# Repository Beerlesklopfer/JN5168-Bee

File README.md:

# JN5168-Bee
Interface and programming Board for JN5168-001-M00Z Module and clones

Annotiantion:</br>
To prevent that some asian manufactuers take profit without any efforts, the schematic and the board mismatch.

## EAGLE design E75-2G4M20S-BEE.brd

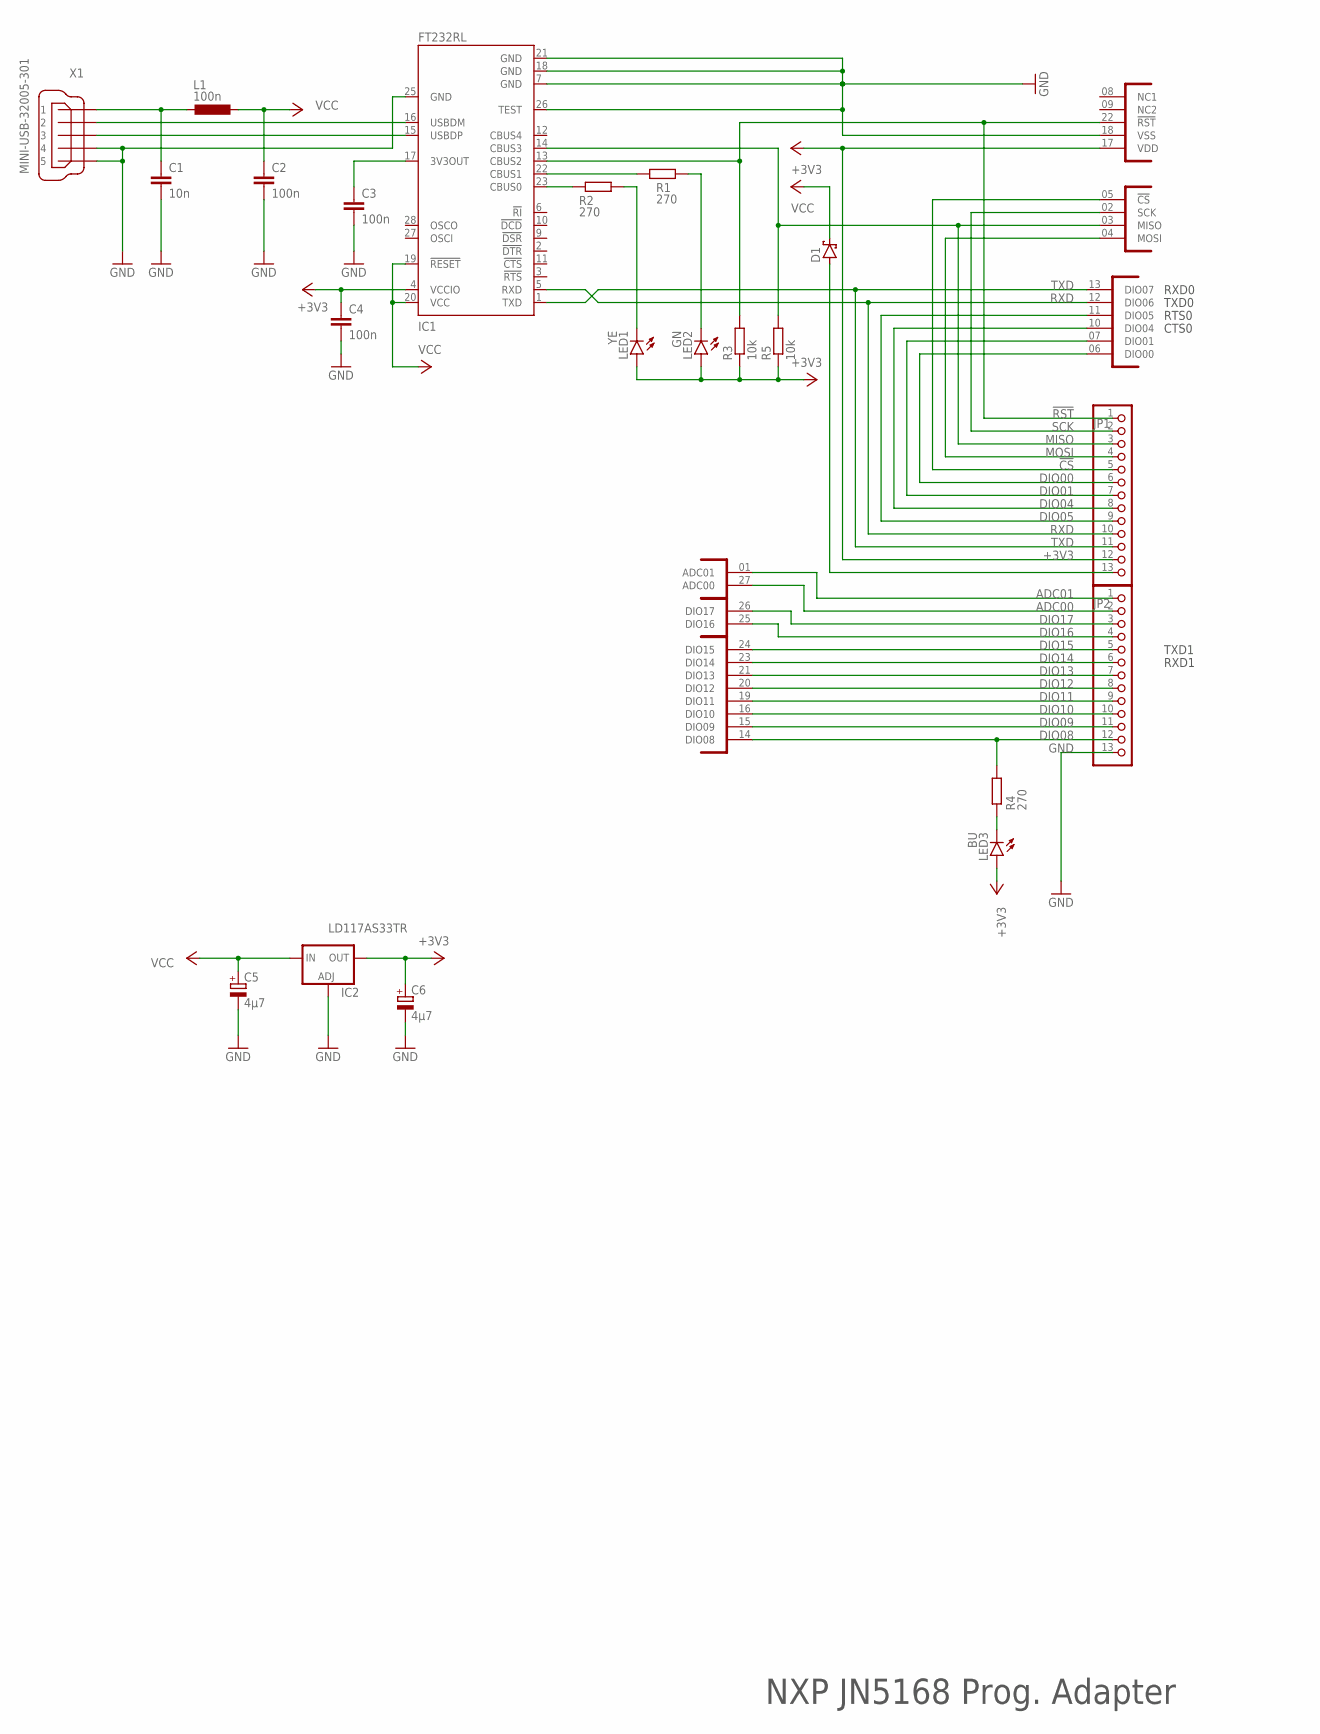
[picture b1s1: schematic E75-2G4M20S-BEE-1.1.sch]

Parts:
C1: 10n; C0805
C2, C3, C4: 100n; C0805
C5, C6: 4µ7; SMC_B
D1: SCHOTTKY-DIODESMD; SMB
IC1: FT232RL; SSOP28
IC2: LD117AS33TR; SOT223
JP1, JP2: PINHD-1X13; 1X13
L1: 100n; L3225P
LED1: YE; CHIP-LED0805
LED2: GN; CHIP-LED0805
LED3: BU; CHIP-LED0805
N1: E75-2G4M20S
R1, R2, R4: 270; R0805W
R3, R5: 10k; M0805
X1: MINI-USB-32005-301; 32005-301

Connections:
!CS: JP1.5, N1.05 (!CS)
!RST: IC1.13 (CBUS2), JP1.1, N1.22 (!RST), R3.2
+3V3: C4.1, C6.+, IC1.4 (VCCIO), IC2.4 (OUT), JP1.12, LED1.A, LED2.A, LED3.A, N1.17 (VDD), R3.1, R5.1
ADC00: JP2.2, N1.27 (ADC00)
ADC01: JP2.1, N1.01 (ADC01)
DIO00: JP1.6, N1.06 (DIO00)
DIO01: JP1.7, N1.07 (DIO01)
DIO04: JP1.8, N1.10 (DIO04)
DIO05: JP1.9, N1.11 (DIO05)
DIO06: IC1.5 (RXD), JP1.10, N1.12 (DIO06)
DIO07: IC1.1 (TXD), JP1.11, N1.13 (DIO07)
DIO08: JP2.12, N1.14 (DIO08), R4.2
DIO09: JP2.11, N1.15 (DIO09)
DIO10: JP2.10, N1.16 (DIO10)
DIO11: JP2.9, N1.19 (DIO11)
DIO12: JP2.8, N1.20 (DIO12)
DIO13: JP2.7, N1.21 (DIO13)
DIO14: JP2.6, N1.23 (DIO14)
DIO15: JP2.5, N1.24 (DIO15)
DIO16: JP2.4, N1.25 (DIO16)
DIO17: JP2.3, N1.26 (DIO17)
DM: IC1.16 (USBDM), X1.2
DP: IC1.15 (USBDP), X1.3
GND: C1.2, C2.2, C3.2, C4.2, C5.-, C6.-, IC1.7 (GND), IC1.18 (GND), IC1.21 (GND), IC1.25 (GND), IC1.26 (TEST), IC2.1 (ADJ), JP2.13, N1.18 (VSS), X1.4, X1.5
MISO: IC1.14 (CBUS3), JP1.3, N1.03 (MISO), R5.2
MOSI: JP1.4, N1.04 (MOSI)
unnamed: C3.1, IC1.17 (3V3OUT)
unnamed: LED3.C, R4.1
unnamed: C1.1, L1.2, X1.1
unnamed: IC1.23 (CBUS0), R2.1
unnamed: D1.A, JP1.13
unnamed: IC1.22 (CBUS1), R1.1
unnamed: LED1.C, R2.2
unnamed: LED2.C, R1.2
SCK: JP1.2, N1.02 (SCK)
VCC: C2.1, C5.+, D1.C, IC1.19 (!RESET), IC1.20 (VCC), IC2.3 (IN), L1.1

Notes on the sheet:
NXP JN5168 Prog. Adapter
TXD0
RXD0
RTS0
CTS0
TXD1
RXD1

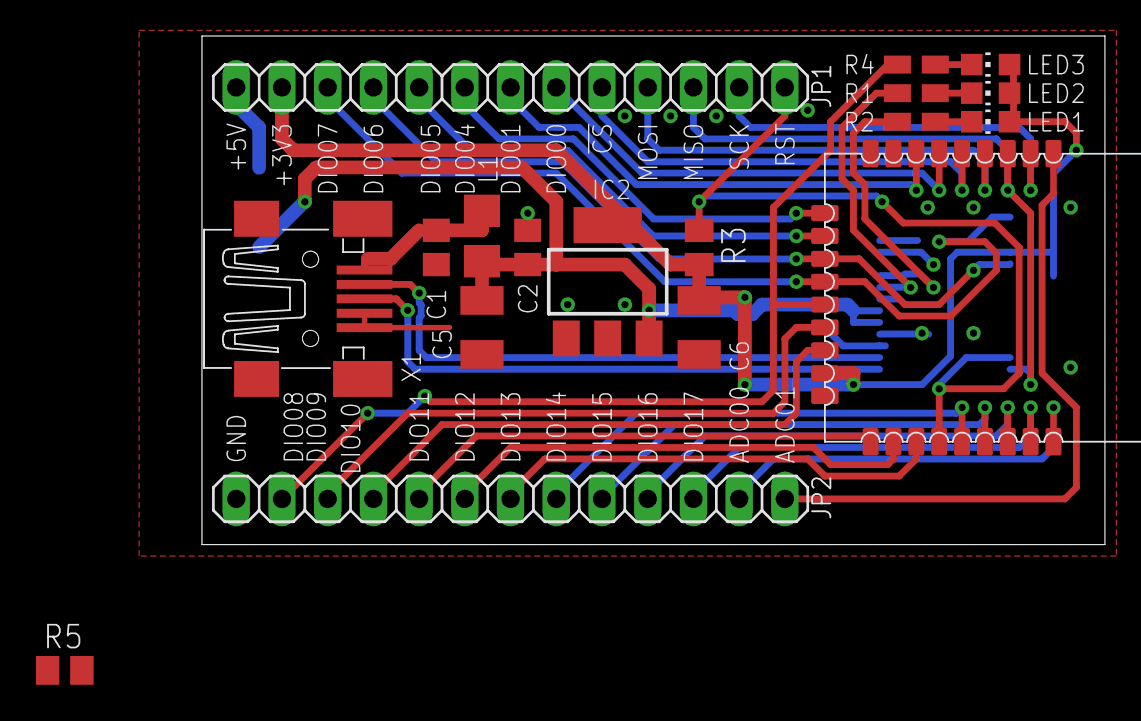
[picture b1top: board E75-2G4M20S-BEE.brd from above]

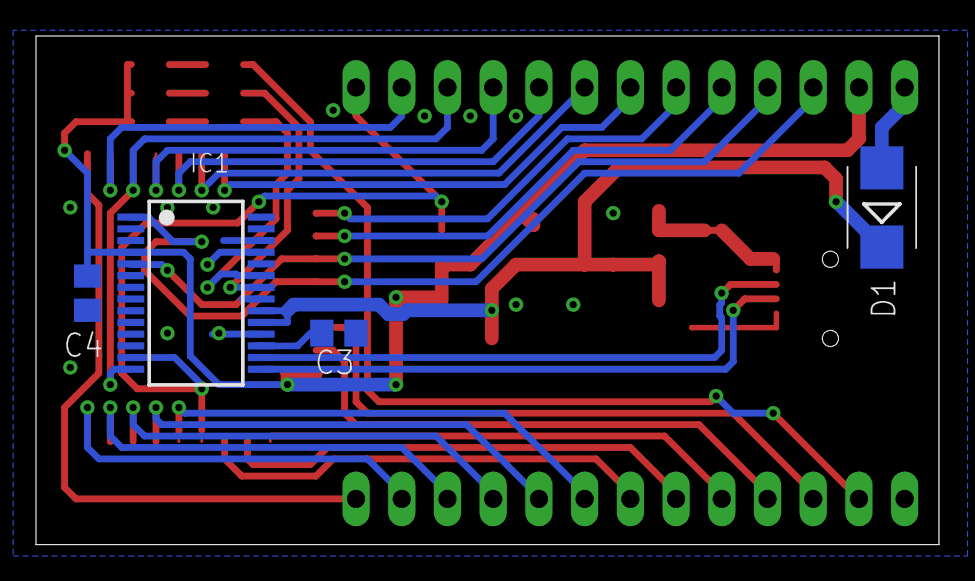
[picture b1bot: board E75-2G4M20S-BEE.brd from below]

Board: 2 copper layers, 50.2 x 28.3 mm, 22 parts (4 on the bottom side), 36 nets.

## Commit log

2019-02-17 Images Uploaded
